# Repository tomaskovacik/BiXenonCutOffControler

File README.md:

# BiXenonCutOffControler

Simple board which enable bi-xenon cutoff selenoid only if low beams are turned on or disable it when low beams are turned off. When your car is using [PWM](https://en.wikipedia.org/wiki/Pulse-width_modulation) to drive your high beam bulbs at ~30% to act as daytime driving lights, connecting bixenon cuttoff selenoid paralel to high beam bulb will cause nasty rattling noise of this selenoid. 

# Schematics

Single Nchannel mosfet is turned on when low beams are enabled. This mosfet grounds one side of selenoid which is then turned on when high beams are used.

# In action

https://youtu.be/b0E2H7acrZI

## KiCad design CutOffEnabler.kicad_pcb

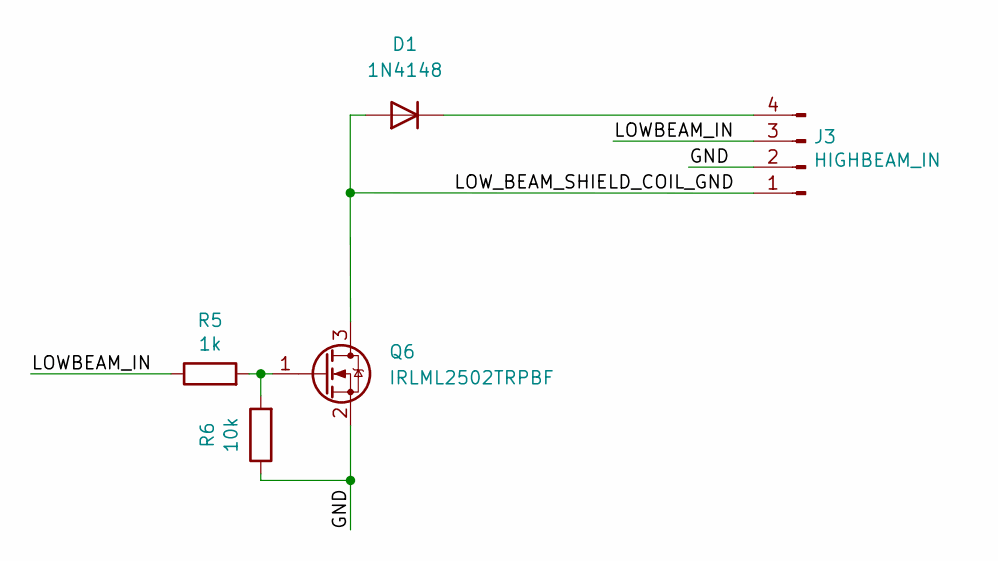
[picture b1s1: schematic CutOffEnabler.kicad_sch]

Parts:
D1: 1N4148; D_DO-35_SOD27_P7.62mm_Horizontal
J3: HIGHBEAM_IN; Molex_MiniFit-JR-5569-04A2_2x02x4.20mm_Angled
Q6: IRLML2502TRPBF; SOT-23
R5: 1k; R_0805_HandSoldering
R6: 10k; R_0805_HandSoldering

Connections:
/GND: J3.2, Q6.2 (S), R6.1
/LOWBEAM_IN: J3.3, R5.1
/LOW_BEAM_SHIELD_COIL_GND: D1.2 (A), J3.1, Q6.3 (D)
unnamed: D1.1 (K), J3.4
unnamed: Q6.1 (G), R5.2, R6.2

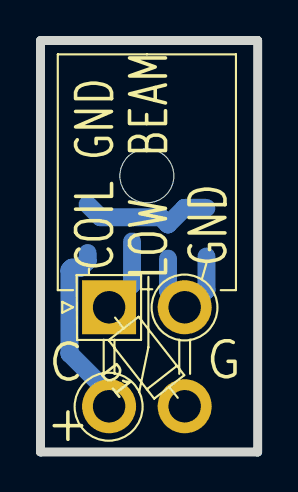
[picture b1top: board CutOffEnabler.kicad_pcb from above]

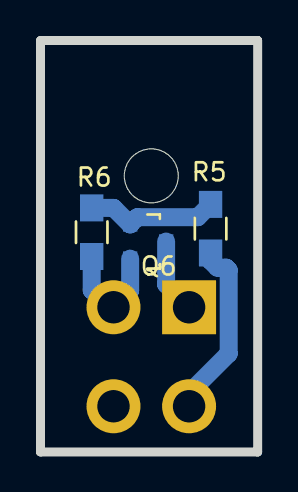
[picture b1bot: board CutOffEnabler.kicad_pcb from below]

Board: 2 copper layers, 12.1 x 22.9 mm, 5 parts (3 on the bottom side), 5 nets.

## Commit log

2021-08-09 Create LICENSE
2021-08-09 howtoconnect
2021-08-09 pics
2021-08-09 ibom_for_hw
2021-08-09 schematics
2021-08-09 new_schematics
2021-08-09 del_schematics
2021-08-10 pic of 2 module for tindie
2021-08-10 new picture of modules
2021-08-10 tindie badge
